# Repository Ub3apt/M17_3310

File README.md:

# M17_3310
Mainboard replacement for Nokia 3310

## Photos
Both photos in the `misc` directory are cropped, so that if you scale them for 108mm height, you should be able to make direct measurements using GIMP or other image editing software.

## Firmware
See the example firmware [here](https://github.com/M17-Project/M17_3310-fw).

## Зачем это надо.
Проект позволяет изготовить на фабрике и использовать замаскированый под сотовый телефон компактную радиостанцию работающую по цифровому протоколу М17 с цифровыми ретранляторами, сетями и радиостанциями.  

## Подробное описание на Википедии. 
https://en.wikipedia.org/wiki/M17_(amateur_radio) 

М17 является цифровой режим радиомодуляции разработан Войцехом Качмарским (Wojciech Kaczmarski). M17 в первую очередь предназначен для голосовой связи на УКВ радиолюбителями и прочими.

M17 использует Частота-Разделение Множественный Доступ (FDMA) технология, в которой разные потоки связи разделены по частоте и запускаются одновременно. Он использует 4800 символов в секунду, 4-уровневый частотно-сдвиговая клавиша (4FSK) с а корневой фильтр Найквиста применяется к битовому потоку. Радиоканалы шириной 9 кГц, с интервалом канала 12,5 кГц. валовая скорость передачи данных составляет 9600 бит в секунду, при фактической передаче данных - 3200. Передача, называемая поток, делится на 40-миллисекундную длину кадра, каждая из них дополнена 16-битным длинным словом синхронизации. Группа из 6 кадров образует суперкадр и необходим для декодирования данных информации о ссылках. Протокол позволяет осуществлять низкоскоростную передачу данных (наряду с голосом), например. GNSS данные о положении. Режим успешно передан через EchoStar XXI  и КО-100 геостационарные спутники. Спецификация протокола выпущена под GNU General Public License.

M17 использует Кодек 2низкобитретный голосовой кодек, разработанный Дэвидом Роу VK5DGR и др. Codec 2 был разработан для использования для любительского радио и других голосовых приложений с высокой степенью сжатия. В его основе лежит линейное предсказательное кодирование при смешанно-гармоническом синусоидальном возбуждении. Протокол поддерживает как 3200 (полноценный), так и 1600 бит в секунду (полускоростной) режимы.

Протокол M17 был в первую очередь предназначен для радиолюбительского использования.

  Кодирование Позывного: 48-битное поле, содержащее до 9 буквенно-цифровых символов, устраняет необходимость централизованной базы данных пользовательских ID.
Потоковый и пакетный режимы работы.
Режим потока предлагает один канал с чистым битрейтом 3200 bps (кодированная речь или данные) или два канала с частотой 1600bps (кодированная речь наряду с данными).
Режим пакетов поддерживает обмен текстовыми сообщениями, АПРС и AX.25.
Медленно-скоростной боковой канал для короткой и повторной передачи данных, например. Данные о положении ГНСС или телеметрия.
Шифрование:
Битовое шифрование скремблера: а псевдослучайная двоичная последовательность создан путем объединения эксклюзивно-побочная работа на аудио или потоке данных и сдвиговый регистр с линейной обратной связью используя один из 3 многочлены обратной связи с 255, 65 535 и 16 777 215-битными периодами повторения.
AES шифрование: 128-битный блочный шифр, работающий в режим CTR с выбираемым пользователем ключом 128, 192 или 256 бит.

С небольшой аппаратной модификацией портативные приемопередатчики TYT MD-380, MD-390 и MD-UV380 могут быть оснащены пользовательской бесплатной прошивкой с открытым исходным кодом[12] чтобы включить поддержку M17.

Приложения и проекты с поддержкой M17
OpenRTX - бесплатная прошивка с открытым исходным кодом для ветчинных радиостанций
WPSD - цифровой голосовой программный комплекс для любительского радио персональных точек доступа и ретрансляторов
DroidStar - цифровой голосовой клиент для Android
Многорежимный Цифровой Голосовой Модем (MMDVM)
SDR++ - мультиплатформенный, программно-ориентированный радиоприемник с открытым исходным кодом
SDRangel - мультиплатформенное программное обеспечение с открытым исходным кодом, определяемое радиоприемником/передатчиком
OpenWebRX - веб-программный радиоприемник
отражатель Мрефд - М17[22]
rpitx - общий радиочастотный передатчик для Raspberry Pi[23]
dsd-fme - цифровой декодер речи[24]
mvoice - голосовой клиент и графический ретранслятор (Raspberry и Linux)

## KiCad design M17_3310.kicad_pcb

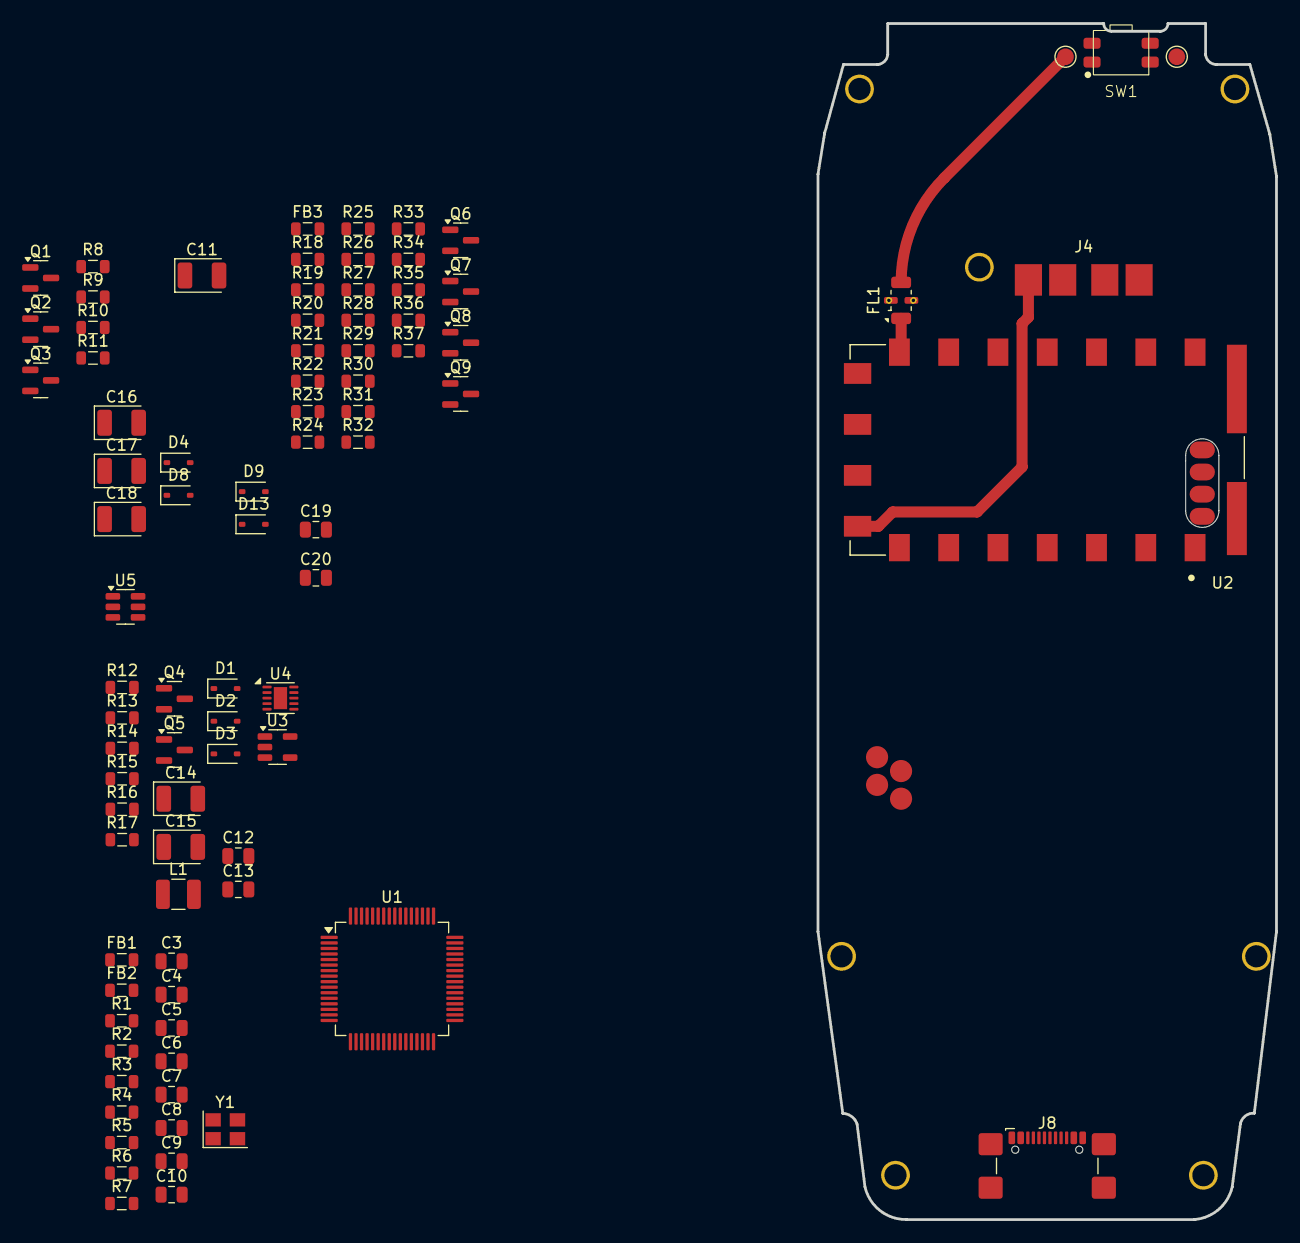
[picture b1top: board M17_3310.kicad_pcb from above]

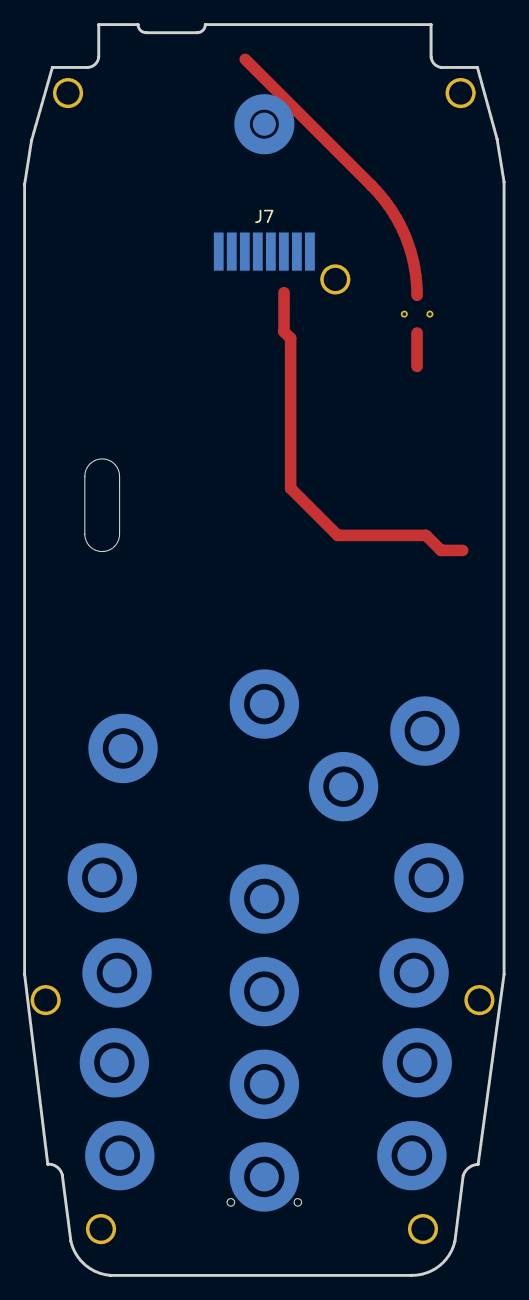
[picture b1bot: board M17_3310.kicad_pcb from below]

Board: 4 copper layers, 41.4 x 108.0 mm, 113 parts (18 on the bottom side), 66 nets.

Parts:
C3, C4: 2u2; C_0805_2012Metric
C5, C6, C7, C8, C9, C10, C12, C13, C19: 100n; C_0805_2012Metric
C11, C17, C18: 47uF/10V; CP_EIA-3528-21_Kemet-B
C14, C15, C16: 10uF/10V; CP_EIA-3528-21_Kemet-B
C20: 10n; C_0805_2012Metric
D1, D2, D3, D4, D8, D9, D13: BAT60A; D_SOD-323
FB1, FB2, FB3: Bead; L_0805_2012Metric
FL1: LFCN-490+; Filter_Mini-Circuits_FV1206
H1, H2, H3, H4, H5, H6, H7: 2mm_mounting_hole_sig
J1: SWD_DBG; 3310_4_pin
J2: ANT_A; TestPoint_Pad_D1.5mm
J3: ANT_B; TestPoint_Pad_D1.5mm
J4: Battery; 3310_batt
J7: Display; 3310_display
J8: USB C; USB_C_Receptacle_GCT_USB4110
L1: 1u5; L_1210_3225Metric
LS1: 3310_speaker
Q1, Q3, Q4, Q6, Q7, Q9: BSS138; SOT-23
Q2, Q8: IRLML6401; SOT-23
Q5: BSS84; SOT-23
R1, R5: 22k; L_0805_2012Metric
R2: 2k2; L_0805_2012Metric
R3, R4, R9, R11, R12, R15, R20, R33, R34, R35, R36, R37: 47k; L_0805_2012Metric
R6: 10k; L_0805_2012Metric
R7, R8, R10, R13, R14, R17, R19, R22: 100k; L_0805_2012Metric
R16, R30: 1k; L_0805_2012Metric
R18: 47R; L_0805_2012Metric
R21, R23, R24, R25, R26, R27, R28, R29: 27R; L_0805_2012Metric
R31, R32: 5k1; L_0805_2012Metric
SW1: POWER ON; SIDE PUSH 2.2NF 4.7x3.2x1.65mm
SW2: "OK"; 3310_key
SW3, SW4, SW5, SW6, SW7, SW8, SW9, SW10, SW11, SW12, SW13, SW14, SW15, SW16, SW17: 3310_key
U1: STM32F405RGTx; LQFP-64_10x10mm_P0.5mm
U2: SA868; SA868-VER1.1
U3: MAX1555; TSOT-23-5
U4: TPS63030DSK; WSON-10-1EP_2.5x2.5mm_P0.5mm_EP1.2x2mm
U5: USBLC6-2SC6; SOT-23-6
Y1: 8MHz; Crystal_SMD_3225-4Pin_3.2x2.5mm

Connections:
+3V3: C14.1, C15.1, C17.1, D3.2 (A), D4.1 (K), D8.1 (K), D9.1 (K), D13.1 (K), FB1.2, FB2.1, J7.8, Q8.2 (S), R6.1, R20.2, R30.2, U4.1 (VOUT), U4.10 (FB)
/COL_1: SW3.1, SW4.1, SW5.1, SW6.1, SW7.1
/COL_2: SW8.1, SW9.1, SW10.1, SW11.1, SW12.1
/COL_3: SW13.1, SW14.1, SW15.1, SW16.1, SW17.1
/Interfaces/5V_USB: C18.1, D1.2 (A), FB3.1, U3.1 (USB), U3.4 (DC)
/Interfaces/BOOT0: R1.1, SW2.1, U1.60 (BOOT0)
/Interfaces/BUZZ: Q9.1 (G), R22.2
/Interfaces/DISP_D/C: J7.5, U1.59 (PB7)
/Interfaces/DISP_SCK: J7.7, U1.55 (PB3)
/Interfaces/DISP_SDIN: J7.6, U1.57 (PB5)
/Interfaces/UDB_DM: U1.44 (PA11), U5.1 (I/O1)
/Interfaces/USB_DP: U1.45 (PA12), U5.3 (I/O2)
/Interfaces/VIBR: Q6.1 (G), R17.2
/Interfaces/~DISP_CE: J7.4, U1.58 (PB6)
/Interfaces/~DISP_RST: J7.1, U1.61 (PB8)
/MCU/BATT_MEAS: C12.2, R11.1, R12.2, U1.15 (PA1)
/MCU/BSB_IN: R3.1, R4.2, U1.14 (PA0), U2.3 (AF_OUT)
/MCU/BSB_OUT: U1.20 (PA4), U2.18 (MIC_IN)
/MCU/MCU_VDD: C7.1, C8.1, C9.1, C10.1, FB2.2, R2.1, U1.19 (VDD), U1.32 (VDD), U1.48 (VDD), U1.64 (VDD)
/MCU/MCU_VDDA: C6.2, FB1.1, R3.2, U1.13 (VDDA)
/MCU/NRST: J1.1, R2.2, U1.7 (NRST)
/MCU/PWR_ON: Q4.1 (G), R14.2, U1.36 (PB15)
/MCU/RF_ENA: Q3.1 (G), R10.2
/MCU/RF_PWR: Q1.1 (G), R7.2
/MCU/RTC_BATT: C5.2, R16.1, U1.1 (VBAT)
/MCU/SWCLK: J1.3, U1.49 (PA14)
/MCU/SWDIO: J1.2, U1.46 (PA13)
/MCU/X1: U1.5 (PH0), Y1.1
/MCU/X2: U1.6 (PH1), Y1.3
/MCU/~CHG: R6.2, U1.35 (PB14), U3.3 (~CHG)
/PMU/U_BATT: C11.1, D2.2 (A), J4.1, Q2.2 (S), R8.2, R11.2, U2.8 (V_{BAT}), U3.5 (BAT)
/ROW_1: R33.2, SW3.2, SW8.2, SW13.2
/ROW_2: R34.2, SW4.2, SW9.2, SW14.2
/ROW_3: R35.2, SW5.2, SW10.2, SW15.2
/ROW_4: R36.2, SW6.2, SW11.2, SW16.2
/ROW_5: R37.2, SW7.2, SW12.2, SW17.2
GND: C3.1, C4.1, C5.1, C6.1, C7.2, C8.2, C9.2, C10.2, C11.2, C12.1, C13.1, C14.2, C15.2, C16.2, C17.2, C18.2, C19.2, C20.2, FL1.2 (GND), FL1.4 (GND), H1.1, H2.1, H3.1, H4.1, H5.1, H6.1, H7.1, J1.4, J3.1, J4.4, J7.3, J8.A1 (GND), J8.A12 (GND), J8.B1 (GND), J8.B12 (GND), J8.S1 (SHIELD), Q1.2 (S), Q3.2 (S), Q4.2 (S), Q6.2 (S), Q7.2 (S), Q9.2 (S), R1.2, R4.1, R5.1, R7.1, R9.1, R10.1, R12.1, R14.1, R15.1, R17.1, R19.1, R22.1, R31.2, R32.2, R33.1, R34.1, R35.1, R36.1, R37.1, U1.12 (VSSA), U1.18 (VSS), U1.63 (VSS), U2.9 (GND), U2.10 (GND), U3.2 (GND), U4.3 (PGND), U4.9 (GND), U4.11 (PGND), U5.2 (GND), Y1.2, Y1.4
unnamed: D1.1 (K), D2.1 (K), Q5.2 (S), R13.2, SW1.2, SW1.4 (A), U4.5 (VIN)
unnamed: D3.1 (K), R16.2
unnamed: D4.2 (A), Q6.3 (D)
unnamed: D8.2 (A), Q9.3 (D)
unnamed: D9.2 (A), R25.2
unnamed: D13.2 (A), R29.2
unnamed: FL1.1 (IN), U2.12 (ANT)
unnamed: FL1.3 (OUT), J2.1
unnamed: C16.1, J7.2
unnamed: J8.A5 (CC1), R31.1
unnamed: J8.B5 (CC2), R32.1
unnamed: J8.A6 (D+), J8.B6 (D+), U5.4 (I/O2)
unnamed: J8.A7 (D-), J8.B7 (D-), U5.6 (I/O1)
unnamed: Q1.3 (D), U2.7 (H/L)
unnamed: Q2.3 (D), R9.2, U2.6 (PD)
unnamed: Q2.1 (G), Q3.3 (D), R8.1
unnamed: Q4.3 (D), Q5.1 (G), R13.1
unnamed: Q5.3 (D), R15.2, SW1.1, SW1.3 (K), U4.6 (EN)
unnamed: Q7.3 (D), Q8.1 (G), R20.1
unnamed: Q7.1 (G), R18.2, R19.2
unnamed: Q8.3 (D), R21.1, R23.1, R24.1, R25.1, R26.1, R27.1, R28.1, R29.1
unnamed: R30.1, SW2.2
unnamed: R5.2, U1.28 (PB2)
unnamed: C3.2, U1.31 (VCAP_1)
unnamed: C4.2, U1.47 (VCAP_2)
unnamed: L1.1, U4.4 (L1)
unnamed: L1.2, U4.2 (L2)
unnamed: C13.2, U4.7 (PS/SYNC), U4.8 (VINA)
unnamed: C19.1, C20.1, FB3.2, J8.A4 (VBUS), J8.A9 (VBUS), J8.B4 (VBUS), J8.B9 (VBUS), U5.5 (VBUS)

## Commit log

2024-10-21 first push
2024-10-21 more stuff
2024-10-23 imported SA868 - thanks, edgetriggered
2024-10-24 interfaces update
2024-10-25 connections
2024-10-25 RF module footprint update
2024-10-25 rf module pins 19..22 adjustment
2024-10-25 audio part
2024-10-28 spk/mic update
2024-10-31 removed audio part
    - added buzzer
    - added battery voltage measurement
2024-10-31 mayhem
    - removed sd card slot
    - started pcb design
    - added nice 3310 photos
2024-10-31 USB C receptacle's PN update
2024-10-31 added vibro+buzzer footprints
2024-11-01 keypad in place
2024-11-01 some pcb updates
    - linked vibrator/buzzer footprints
2024-11-02 pcb update
2024-11-02 more pcb routing
2024-11-02 PDF render
2024-11-05 info on image scaling
2024-11-05 routed BTN_OK
2024-11-22 PCB update
    - added GND vias
2024-11-22 gitignore update
    - ignore zip files generated by pcbway-plugin
2024-11-22 PN update
2024-11-22 "no connection" tags
2024-11-23 fixed DNP tags
2024-12-13 U5 value update
    TPS63030 is a regulated version of the 3.3V TPS63031. The latter is correct.
2025-01-23 Update README.md
    Дополнение к описанию проекта
